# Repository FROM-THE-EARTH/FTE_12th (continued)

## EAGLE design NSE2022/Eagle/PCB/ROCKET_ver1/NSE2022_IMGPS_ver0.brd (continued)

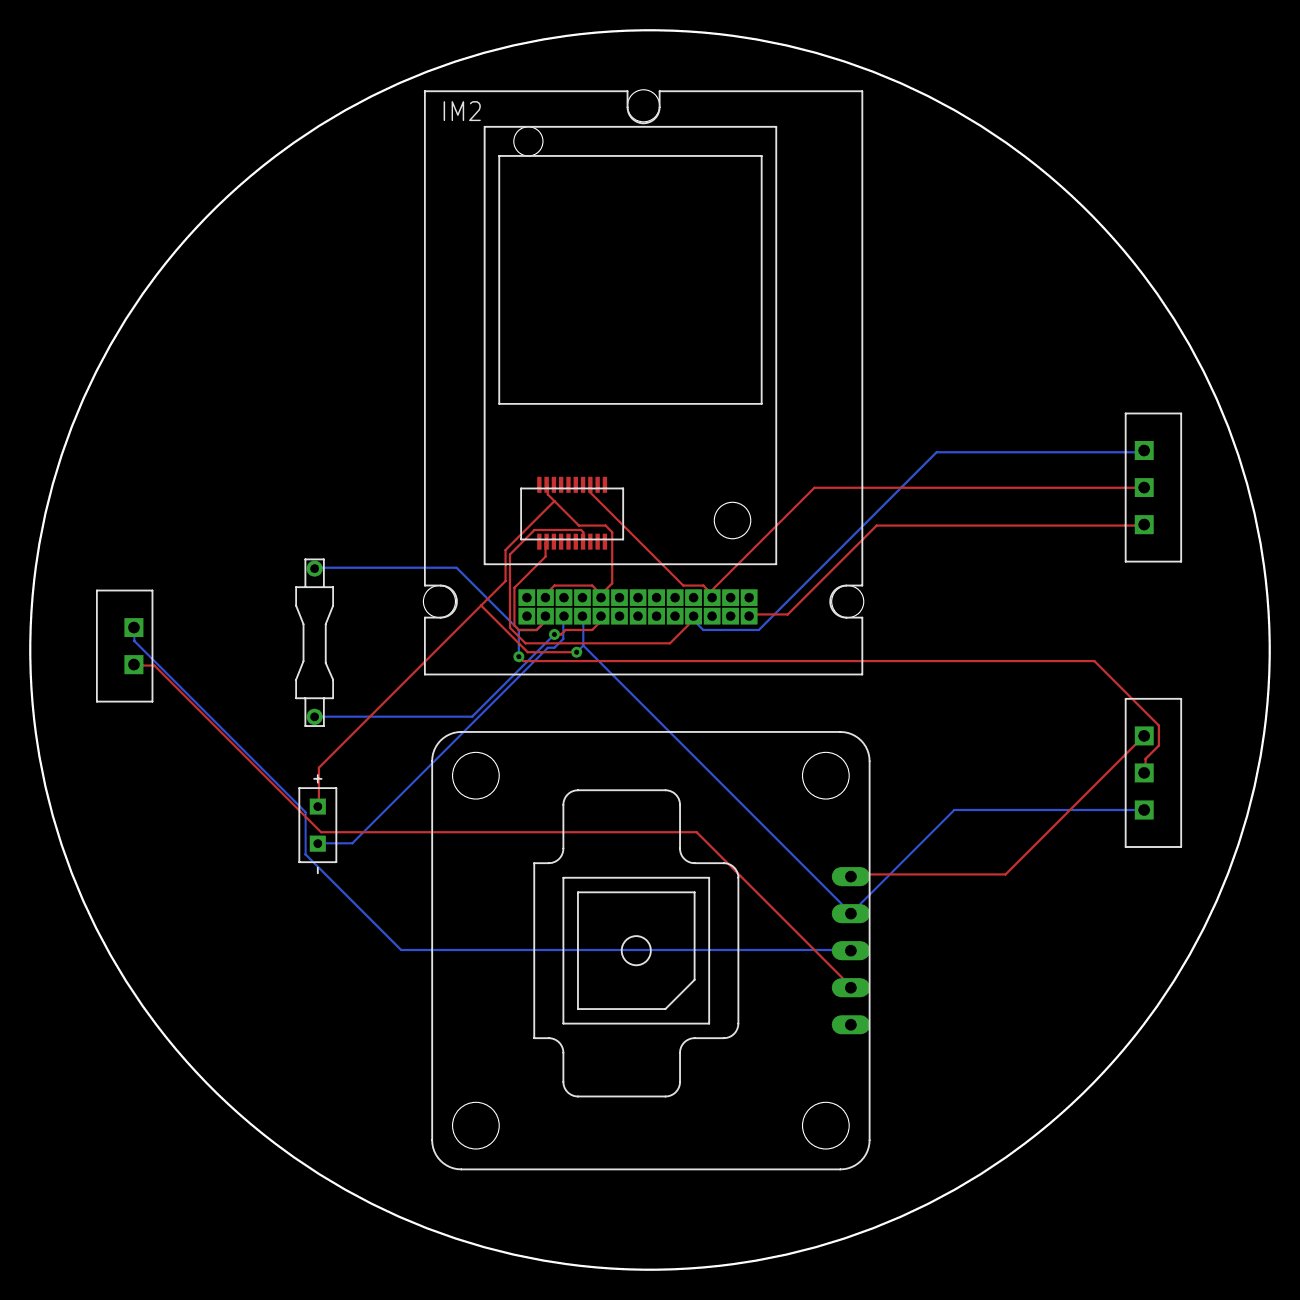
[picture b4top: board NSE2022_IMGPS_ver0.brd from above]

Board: 2 copper layers, 85.0 x 85.0 mm, 8 parts (0 on the bottom side), 10 nets.

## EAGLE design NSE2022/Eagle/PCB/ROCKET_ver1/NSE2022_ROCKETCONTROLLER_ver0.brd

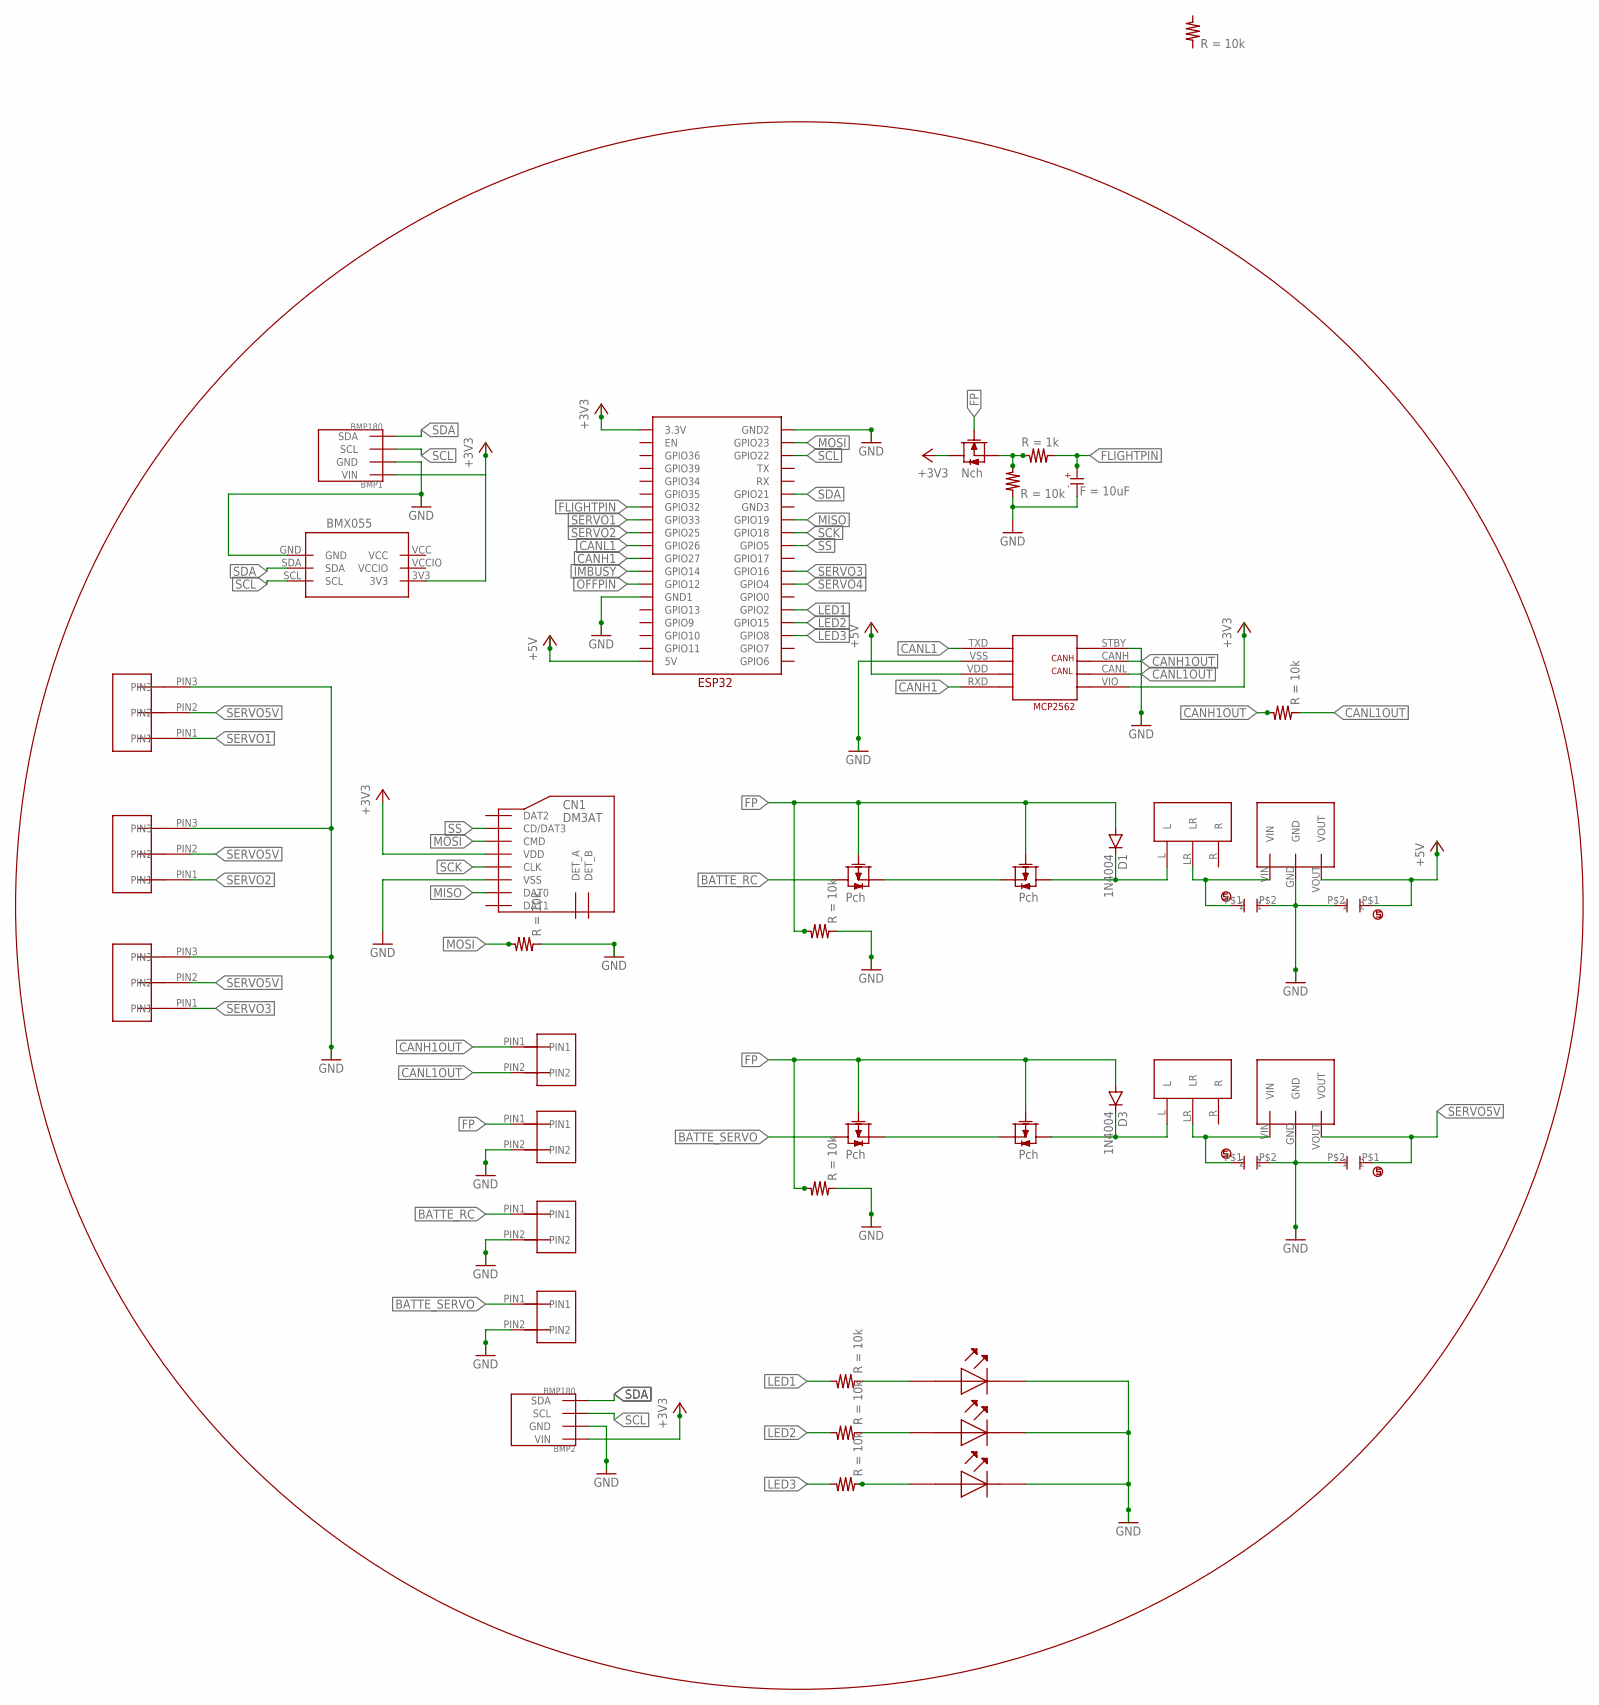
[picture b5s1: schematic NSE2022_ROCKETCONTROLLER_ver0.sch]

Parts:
BMP1, BMP2: BMP180; GY-68
BMX1: BMX055
C1: CAPACITOR-ELECTROLYTIC_1
CERAMIC_CAPACITOR3, CERAMIC_CAPACITOR4, CERAMIC_CAPACITOR5, CERAMIC_CAPACITOR6: CERAMIC_CAPACITOR
CN1: DM3AT
D1, D3: 1N4004; DO41-10
R1, R2, R3, R4, R5, R9, R10, R12, R14, R15: RESISTER; REGISTER
SRIDE_SWTCH1, SRIDE_SWTCH2: SRIDE_SWITCH
U$4: ESP32
U$8: 2SK4017-NCH; 2SK4017
U$12, U$13, U$30, U$31: 2SJ681-PCH; 2SJ681
U$14, U$32: M78AR05-1
U$18, U$19, U$20, U$21: 2PIN
U$27: MCP2562
U$42, U$43, U$44: 3PIN
U$63, U$64, U$69: LED

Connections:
+3V3: BMP1.P1 (VIN), BMP2.P1 (VIN), BMX1.3V3, CN1.VDD, U$4.3.3V, U$8.DRAIN, U$27.VIO
+5V: CERAMIC_CAPACITOR5.P$1 (1), U$4.5V, U$27.VDD, U$32.VOUT
BATTE_RC: U$20.PIN1, U$30.DRAIN
BATTE_SERVO: U$13.DRAIN, U$21.PIN1
CANH1: U$4.GPIO27, U$27.RXD
CANH1OUT: R3.B, U$18.PIN1, U$27.CANH
CANL1: U$4.GPIO26, U$27.TXD
CANL1OUT: R3.A, U$18.PIN2, U$27.CANL
FLIGHTPIN: C1.KS, R10.A, U$4.GPIO32
FP: D1.A, D3.A, R2.B, R5.B, U$8.GATE, U$12.GATE, U$13.GATE, U$19.PIN1, U$30.GATE, U$31.GATE
GND: BMP1.P2 (GND), BMP2.P2 (GND), BMX1.GND, C1.AN, CERAMIC_CAPACITOR3.P$2 (2), CERAMIC_CAPACITOR4.P$2 (2), CERAMIC_CAPACITOR5.P$2 (2), CERAMIC_CAPACITOR6.P$2 (2), CN1.VSS, R2.A, R4.A, R5.A, R9.A, U$4.GND1, U$14.GND, U$19.PIN2, U$20.PIN2, U$21.PIN2, U$27.STBY, U$27.VSS, U$32.GND, U$42.PIN3, U$43.PIN3, U$44.PIN3, U$63.PLUS (OUT), U$64.PLUS (OUT), U$69.PLUS (OUT)
IMBUSY: U$4.GPIO14
LED1: R12.B, U$4.GPIO2
LED2: R14.B, U$4.GPIO15
LED3: R15.B, U$4.GPIO8
MISO: CN1.DAT0, U$4.GPIO19
MOSI: CN1.CMD, R4.B, U$4.GPIO23
unnamed: U$12.SOURCE, U$13.SOURCE
unnamed: R9.B, R10.B, U$8.SOURCE
unnamed: CERAMIC_CAPACITOR4.P$1 (1), SRIDE_SWTCH1.LR, U$14.VIN
unnamed: D1.C, SRIDE_SWTCH2.L, U$31.DRAIN
unnamed: D3.C, SRIDE_SWTCH1.L, U$12.DRAIN
unnamed: R12.A, U$63.MINUS (IN)
unnamed: R14.A, U$64.MINUS (IN)
unnamed: R15.A, U$69.MINUS (IN)
unnamed: U$30.SOURCE, U$31.SOURCE
unnamed: CERAMIC_CAPACITOR6.P$1 (1), SRIDE_SWTCH2.LR, U$32.VIN
OFFPIN: U$4.GPIO12
SCK: CN1.CLK, U$4.GPIO18
SCL: BMP1.P3 (SCL), BMP2.P3 (SCL), BMX1.SCL, U$4.GPIO22
SDA: BMP1.P4 (SDA), BMP2.P4 (SDA), BMX1.SDA, U$4.GPIO21
SERVO1: U$4.GPIO33, U$42.PIN1
SERVO2: U$4.GPIO25, U$43.PIN1
SERVO3: U$4.GPIO16, U$44.PIN1
SERVO4: U$4.GPIO4
SERVO5V: CERAMIC_CAPACITOR3.P$1 (1), U$14.VOUT, U$42.PIN2, U$43.PIN2, U$44.PIN2
SS: CN1.CD/DAT3, U$4.GPIO5
VCC: BMX1.VCC
VCCIO: BMX1.VCCIO

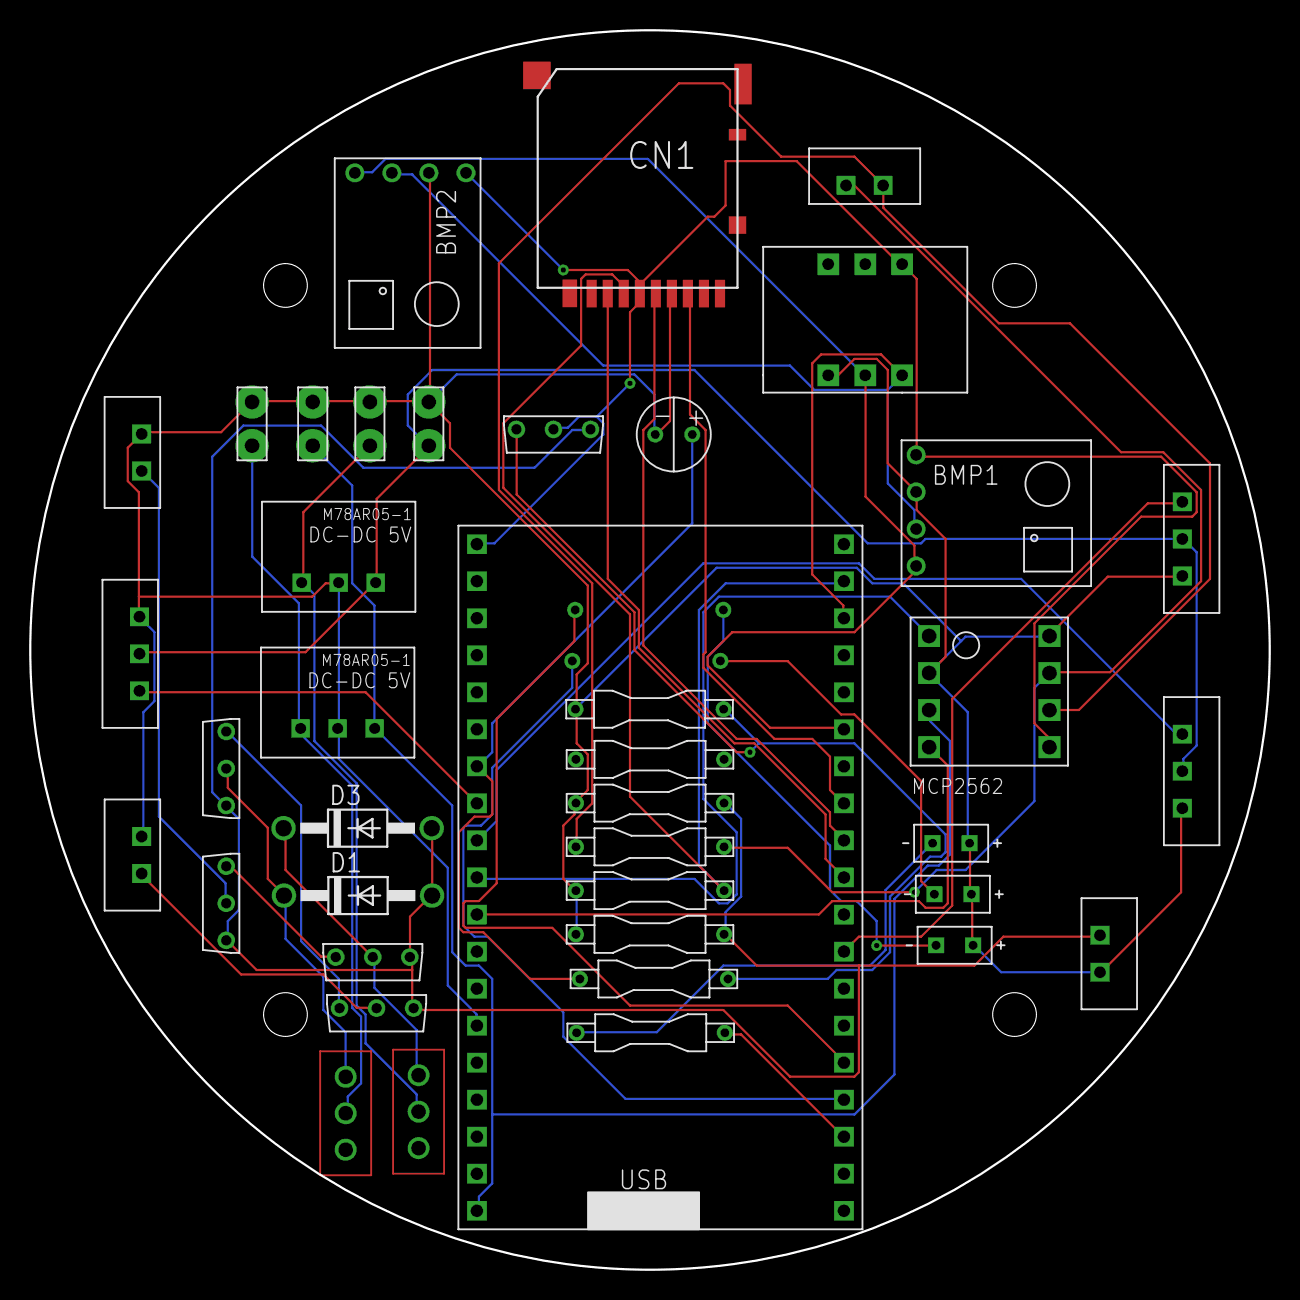
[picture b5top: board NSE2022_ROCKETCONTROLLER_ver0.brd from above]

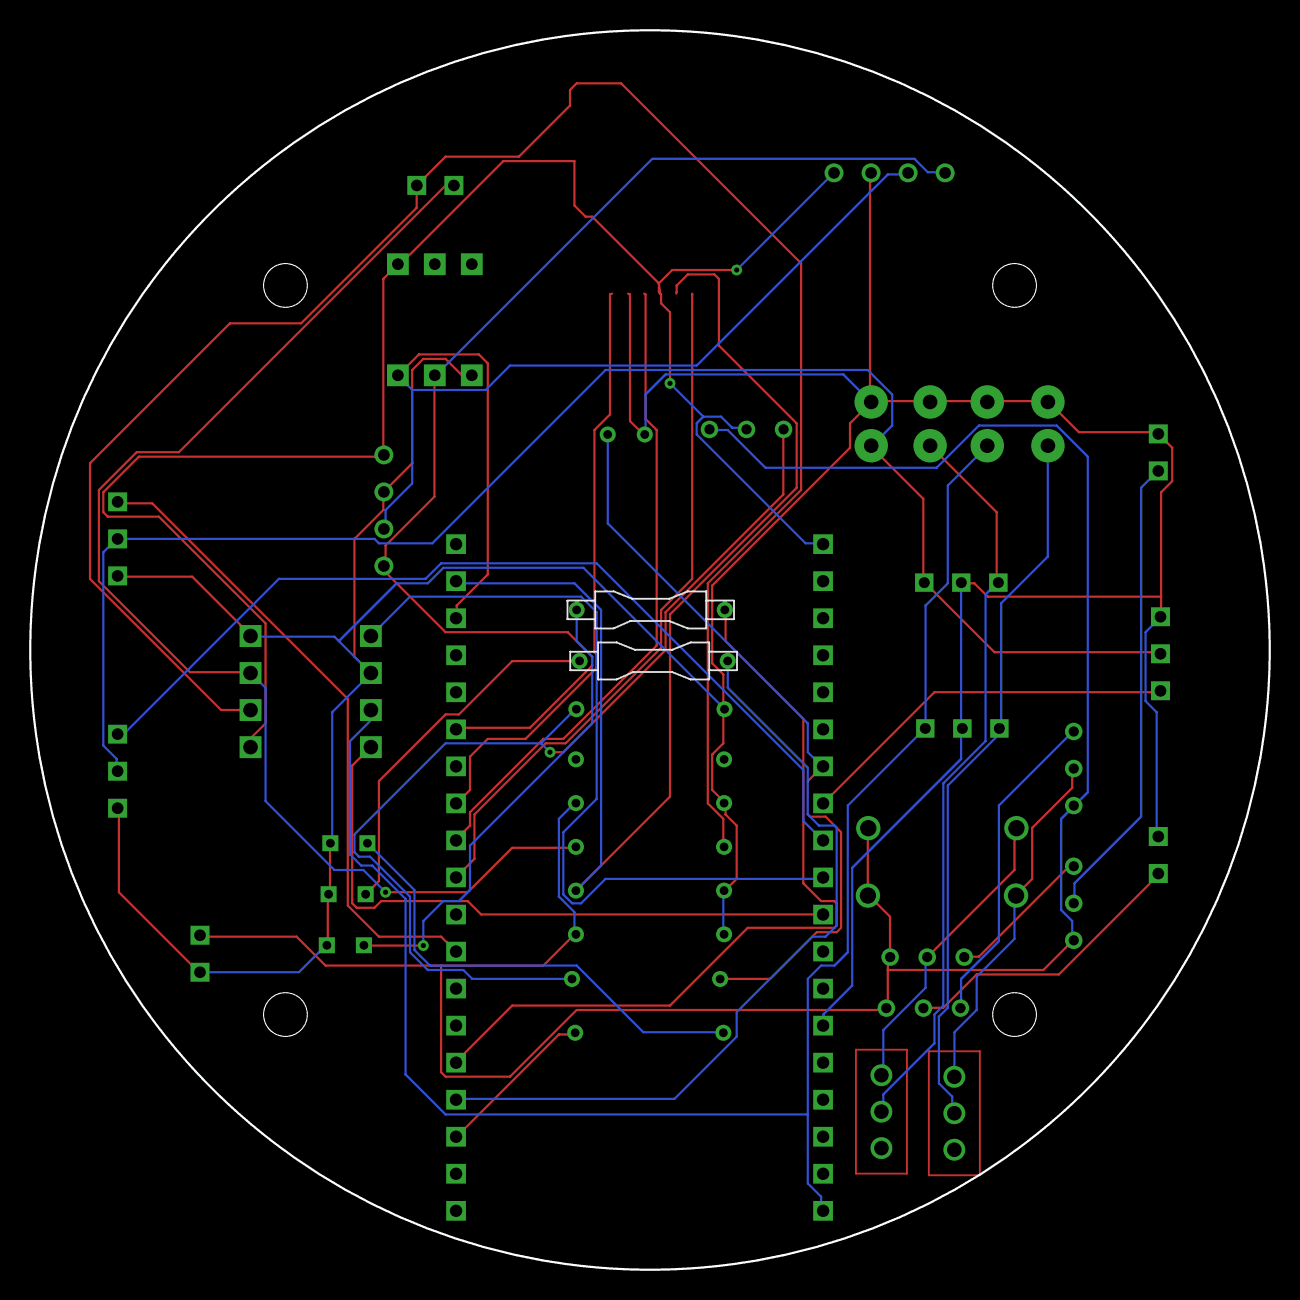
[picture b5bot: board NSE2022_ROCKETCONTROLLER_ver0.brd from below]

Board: 2 copper layers, 85.0 x 85.0 mm, 42 parts (2 on the bottom side), 34 nets.
